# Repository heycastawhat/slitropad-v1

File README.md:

# The Slitropad!

PCB 

Case made in Fusion 360. Oh how I hate Fusion 360.

Schematic

Wow it fits.

---

# Features
It Has 6 Keys.
Key 1: Play/Pause
Key 2: Skip Forward/Back
Key 3: Slack/Discord Button
Key 4: Apple Music Button
Key 5: Push To Mute 
Key 6: Mission Control
(Its made for a mac, all buttons that open apps take advantage of spotlight)

---
# BOM
- 1x 3D Printed Case
- 6x Blank DSA keycaps
- 6x MX-Style switches
- 4x M3x16mm screws
- 4x M3x5mx4mm heatset inserts
- Seed Studio XIAO RP2040

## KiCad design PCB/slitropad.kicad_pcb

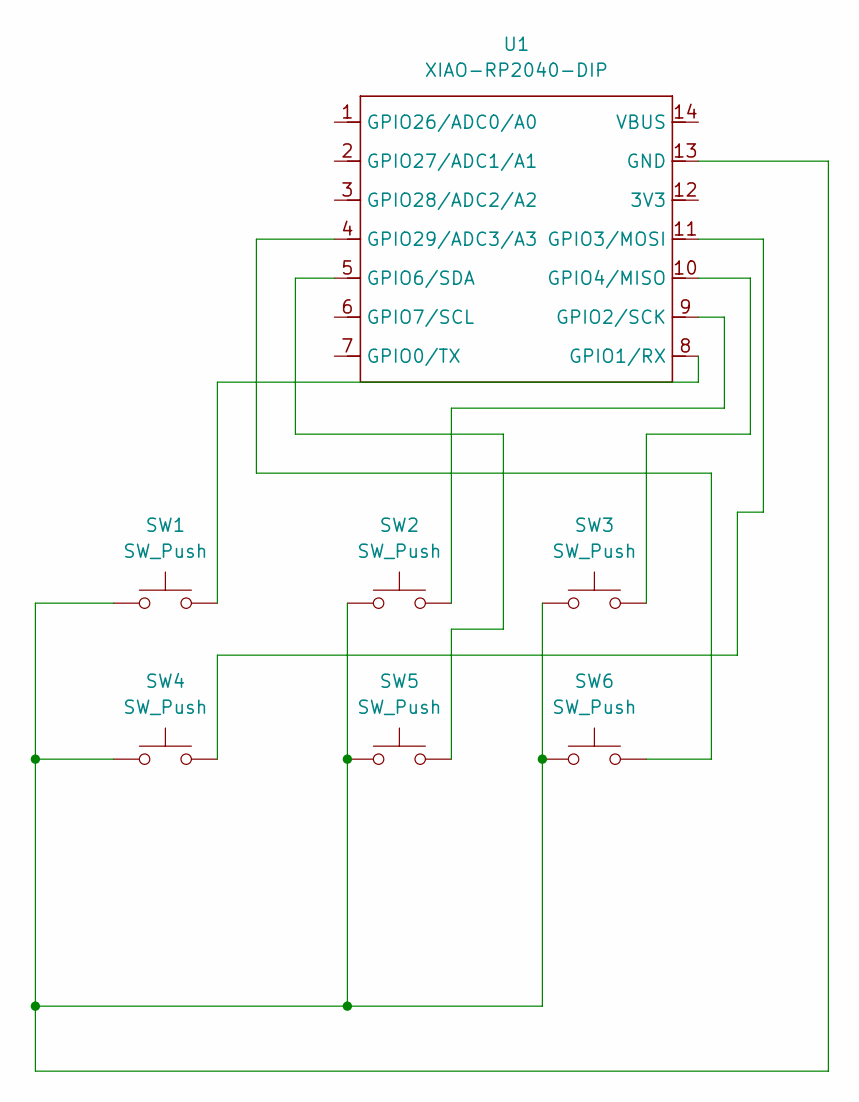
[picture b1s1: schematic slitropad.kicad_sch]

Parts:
SW1, SW2, SW3, SW4, SW5, SW6: SW_Push; SW_Cherry_MX_1.00u_PCB
U1: XIAO-RP2040-DIP

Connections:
unnamed: SW1.1, SW2.1, SW3.1, SW4.1, SW5.1, SW6.1, U1.13 (GND)
unnamed: SW1.2, U1.8 (GPIO1/RX)
unnamed: SW2.2, U1.9 (GPIO2/SCK)
unnamed: SW4.2, U1.11 (GPIO3/MOSI)
unnamed: SW3.2, U1.10 (GPIO4/MISO)
unnamed: SW5.2, U1.5 (GPIO6/SDA)
unnamed: SW6.2, U1.4 (GPIO29/ADC3/A3)

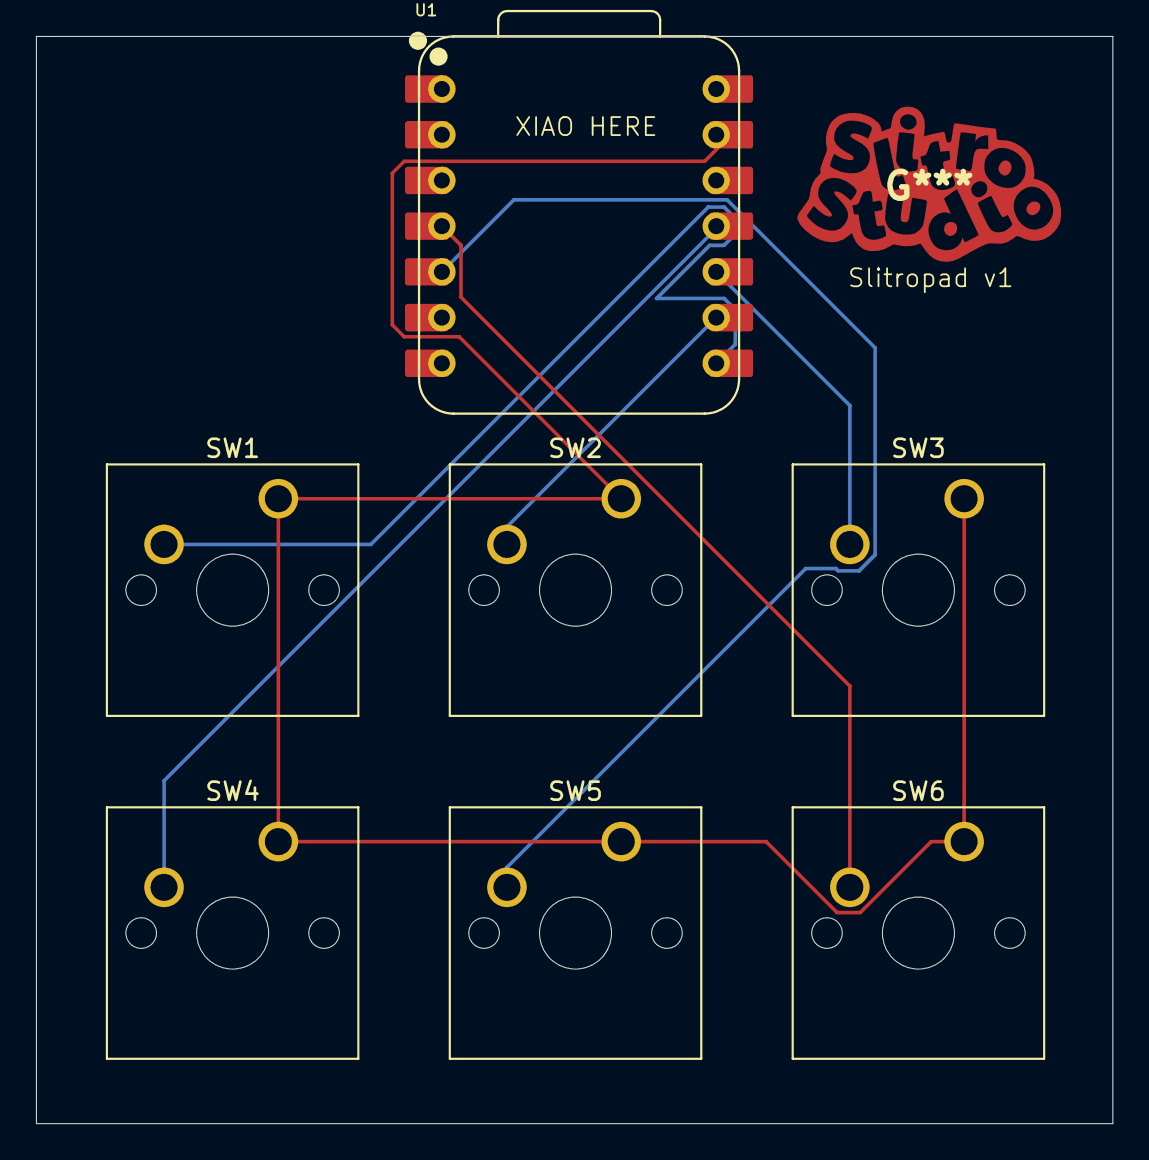
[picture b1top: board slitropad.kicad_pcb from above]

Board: 2 copper layers, 59.8 x 60.4 mm, 7 parts (0 on the bottom side), 7 nets.

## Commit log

2026-01-09 finish firmware and add case
2026-01-09 push
2026-01-09 Update README with images, features, and BOM
    Added images, features, and BOM details to the README.
